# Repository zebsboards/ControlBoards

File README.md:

# ControlBoards
Control boards offered up over the years including 23port Lighting Boards, 24port High Power Boards and cabBlaster Boards

***Each Item is a separate Branch of the main hub***

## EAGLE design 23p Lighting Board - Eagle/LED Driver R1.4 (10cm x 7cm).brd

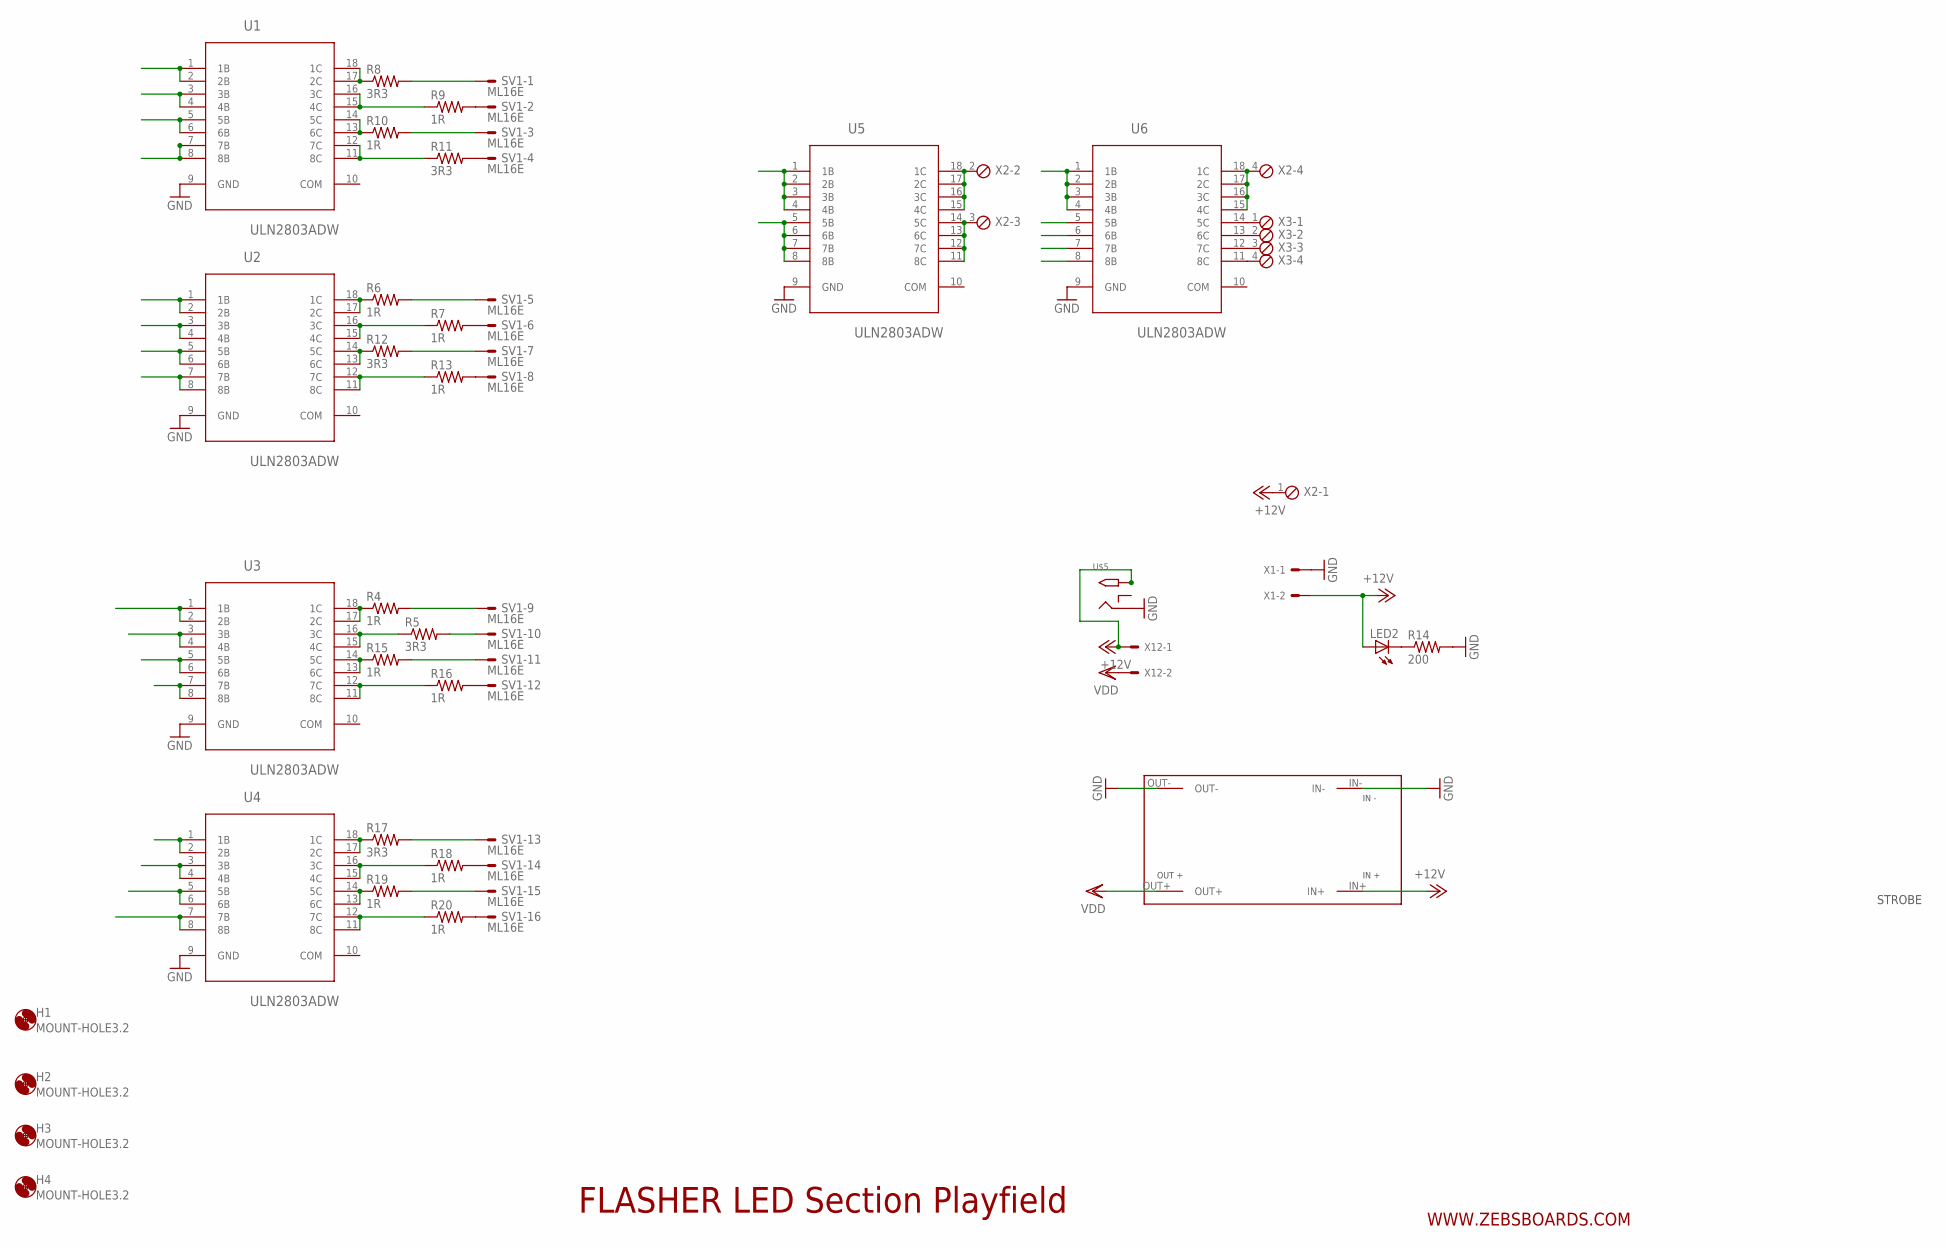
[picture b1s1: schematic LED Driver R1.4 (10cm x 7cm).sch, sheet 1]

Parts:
H1, H2, H3, H4: MOUNT-HOLE3.2; 3,2
LED2: LEDCHIP-LED0805; CHIP-LED0805
R4, R6, R7, R9, R10, R13, R15, R16, R18, R19, R20: 1R; R2010W
R5, R8, R11, R12, R17: 3R3; R2010W
R14: 200; M0805
SV1: ML16E; ML16
U1, U2, U3, U4, U5: ULN2803ADW; SOIC127P1030X265-18N
U6: ULN2803ADW; SOIC127P1030X265-18N; MPN ULN2803ADW
U$1: DC1ACONVERTER; DC1CONVERTER
U$5: 2.1MMJACKTHM; PJ-102A
X1, X12: KK-156-2
X2, X3: MPT4; 4POL254

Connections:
+12V: LED2.A, U$1.IN+, U$5.TIP, X1.2, X2.1, X12.1
D1: U1.1 (1B), U1.2 (2B); also elsewhere on the board
D2: U1.3 (3B), U1.4 (4B); also elsewhere on the board
D3: U1.5 (5B), U1.6 (6B); also elsewhere on the board
D4: U1.7 (7B), U1.8 (8B); also elsewhere on the board
D5: U2.1 (1B), U2.2 (2B); also elsewhere on the board
D6: U2.3 (3B), U2.4 (4B); also elsewhere on the board
D7: U2.5 (5B), U2.6 (6B); also elsewhere on the board
D8: U2.7 (7B), U2.8 (8B); also elsewhere on the board
D9: U3.1 (1B), U3.2 (2B); also elsewhere on the board
D10: U3.3 (3B), U3.4 (4B); also elsewhere on the board
D11: U3.5 (5B), U3.6 (6B); also elsewhere on the board
D12: U3.7 (7B), U3.8 (8B); also elsewhere on the board
D13: U4.1 (1B), U4.2 (2B); also elsewhere on the board
D14: U4.3 (3B), U4.4 (4B); also elsewhere on the board
D15: U4.5 (5B), U4.6 (6B); also elsewhere on the board
D16: U4.7 (7B), U4.8 (8B); also elsewhere on the board
D17: U5.1 (1B), U5.2 (2B), U5.3 (3B), U5.4 (4B); also elsewhere on the board
D18: U5.5 (5B), U5.6 (6B), U5.7 (7B), U5.8 (8B); also elsewhere on the board
D19: U6.1 (1B), U6.2 (2B), U6.3 (3B), U6.4 (4B); also elsewhere on the board
D20: U6.5 (5B); also elsewhere on the board
D21: U6.6 (6B); also elsewhere on the board
D22: U6.7 (7B); also elsewhere on the board
D23: U6.8 (8B); also elsewhere on the board
GND: R14.2, U1.9 (GND), U2.9 (GND), U3.9 (GND), U4.9 (GND), U5.9 (GND), U6.9 (GND), U$1.IN-, U$1.OUT-, U$5.RING, X1.1; also elsewhere on the board
unnamed: R9.1, U1.15 (4C), U1.16 (3C)
unnamed: R8.2, SV1.1
unnamed: R10.2, SV1.3
unnamed: R11.1, U1.11 (8C), U1.12 (7C)
unnamed: R4.1, U3.17 (2C), U3.18 (1C)
unnamed: R5.2, SV1.10
unnamed: R15.1, U3.13 (6C), U3.14 (5C)
unnamed: R8.1, U1.17 (2C), U1.18 (1C)
unnamed: R7.1, U2.15 (4C), U2.16 (3C)
unnamed: R6.2, SV1.5
unnamed: R12.2, SV1.7
unnamed: R13.1, U2.11 (8C), U2.12 (7C)
unnamed: R9.2, SV1.2
unnamed: R10.1, U1.13 (6C), U1.14 (5C)
unnamed: R11.2, SV1.4
unnamed: R6.1, U2.17 (2C), U2.18 (1C)
unnamed: R5.1, U3.15 (4C), U3.16 (3C)
unnamed: R4.2, SV1.9
unnamed: R15.2, SV1.11
unnamed: R16.1, U3.11 (8C), U3.12 (7C)
unnamed: R7.2, SV1.6
unnamed: R12.1, U2.13 (6C), U2.14 (5C)
unnamed: R13.2, SV1.8
unnamed: R16.2, SV1.12
unnamed: R18.1, U4.15 (4C), U4.16 (3C)
unnamed: LED2.C, R14.1
unnamed: R17.2, SV1.13
unnamed: R19.2, SV1.15
unnamed: R20.1, U4.11 (8C), U4.12 (7C)
unnamed: R17.1, U4.17 (2C), U4.18 (1C)
unnamed: R18.2, SV1.14
unnamed: R19.1, U4.13 (6C), U4.14 (5C)
unnamed: R20.2, SV1.16
unnamed: U5.15 (4C), U5.16 (3C), U5.17 (2C), U5.18 (1C), X2.2
unnamed: U5.11 (8C), U5.12 (7C), U5.13 (6C), U5.14 (5C), X2.3
unnamed: U6.15 (4C), U6.16 (3C), U6.17 (2C), U6.18 (1C), X2.4
unnamed: U6.14 (5C), X3.1
unnamed: U6.13 (6C), X3.2
unnamed: U6.12 (7C), X3.3
unnamed: U6.11 (8C), X3.4
VDD: U$1.OUT+, X12.2

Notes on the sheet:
FLASHER LED Section Playfield
WWW.ZEBSBOARDS.COM
STROBE

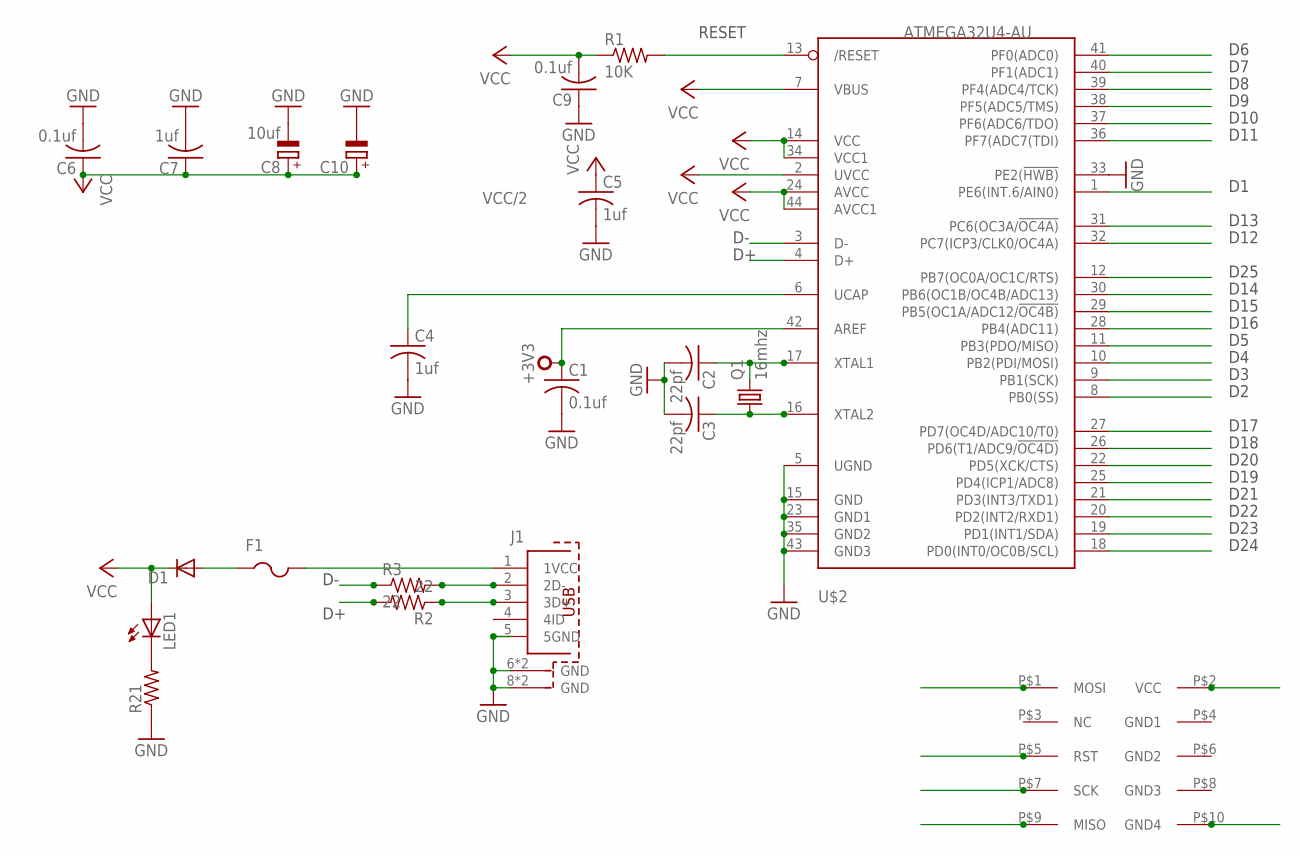
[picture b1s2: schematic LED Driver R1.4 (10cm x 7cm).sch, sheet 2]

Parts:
C1, C6, C9: 0.1uf; C0603
C2, C3: 22pf; C0603
C4, C5, C7: 1uf; C0603
C8: 10uf; A/3216-18W
C10: CPOL-EU153CLV-0605; 153CLV-0605
D1: DIODE-DO214AC; DO214AC
F1: PTCFUSE-1812; 1812
J1: 651005136521
LED1: LEDCHIPLED_0805; CHIPLED_0805
Q1: 16mhz; CTS406
R1: 10K; M0805
R2, R3: 22; M0805
R21: R-US_M0805; M0805
U$2: ATMEGA32U4-AU; TQFP44
U$4: 10PICSP

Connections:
+3V3: C1.1, U$2.42 (AREF)
D1: U$2.1 (PE6(INT.6/AIN0)); also elsewhere on the board
D2: U$2.8 (PB0(SS)); also elsewhere on the board
D3: U$2.9 (PB1(SCK)), U$4.P$7 (SCK); also elsewhere on the board
D4: U$2.10 (PB2(PDI/MOSI)), U$4.P$1 (MOSI); also elsewhere on the board
D5: U$2.11 (PB3(PDO/MISO)), U$4.P$9 (MISO); also elsewhere on the board
D6: U$2.41 (PF0(ADC0)); also elsewhere on the board
D7: U$2.40 (PF1(ADC1)); also elsewhere on the board
D8: U$2.39 (PF4(ADC4/TCK)); also elsewhere on the board
D9: U$2.38 (PF5(ADC5/TMS)); also elsewhere on the board
D10: U$2.37 (PF6(ADC6/TDO)); also elsewhere on the board
D11: U$2.36 (PF7(ADC7(TDI)); also elsewhere on the board
D12: U$2.32 (PC7(ICP3/CLK0/OC4A)); also elsewhere on the board
D13: U$2.31 (PC6(OC3A/!OC4A)); also elsewhere on the board
D14: U$2.30 (PB6(OC1B/OC4B/ADC13)); also elsewhere on the board
D15: U$2.29 (PB5(OC1A/ADC12/!OC4B)); also elsewhere on the board
D16: U$2.28 (PB4(ADC11)); also elsewhere on the board
D17: U$2.27 (PD7(OC4D/ADC10/T0)); also elsewhere on the board
D18: U$2.26 (PD6(T1/ADC9/!OC4D)); also elsewhere on the board
D19: U$2.25 (PD4(ICP1/ADC8)); also elsewhere on the board
D20: U$2.22 (PD5(XCK/CTS)); also elsewhere on the board
D21: U$2.21 (PD3(INT3/TXD1)); also elsewhere on the board
D22: U$2.20 (PD2(INT2/RXD1)); also elsewhere on the board
D23: U$2.19 (PD1(INT1/SDA)); also elsewhere on the board
D24: U$2.18 (PD0(INT0/OC0B/SCL))
D25: U$2.12 (PB7(OC0A/OC1C/RTS))
D+: R2.2, U$2.4 (D+)
D-: R3.1, U$2.3 (D-)
GND: C1.2, C2.2, C3.2, C4.2, C5.2, C6.2, C7.2, C8.-, C9.1, C10.-, J1.5 (5GND), J1.6 (GND), J1.7 (GND), J1.8 (GND), J1.9 (GND), R21.1, U$2.5 (UGND), U$2.15 (GND), U$2.23 (GND1), U$2.33 (PE2(!HWB)), U$2.35 (GND2), U$2.43 (GND3), U$4.P$10 (GND4); also elsewhere on the board
unnamed: C2.1, Q1.3 (2), U$2.17 (XTAL1)
unnamed: C3.1, Q1.1, U$2.16 (XTAL2)
unnamed: C4.1, U$2.6 (UCAP)
unnamed: J1.2 (2D-), R3.2
unnamed: J1.3 (3D+), R2.1
unnamed: F1.2, J1.1 (1VCC)
unnamed: D1.A, F1.1
unnamed: LED1.C, R21.2
RST: R1.2, U$2.13 (/RESET), U$4.P$5 (RST)
VCC: C5.1, C6.1, C7.1, C8.+, C9.2, C10.+, D1.C, LED1.A, R1.1, U$2.2 (UVCC), U$2.7 (VBUS), U$2.14 (VCC), U$2.24 (AVCC), U$2.34 (VCC1), U$2.44 (AVCC1), U$4.P$2 (VCC)

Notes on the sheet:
VCC/2
RESET
D11
D16
D15
D14
D12
D10
D13
D25
D17
D18
D20
D21
D22
D23
D24
D19

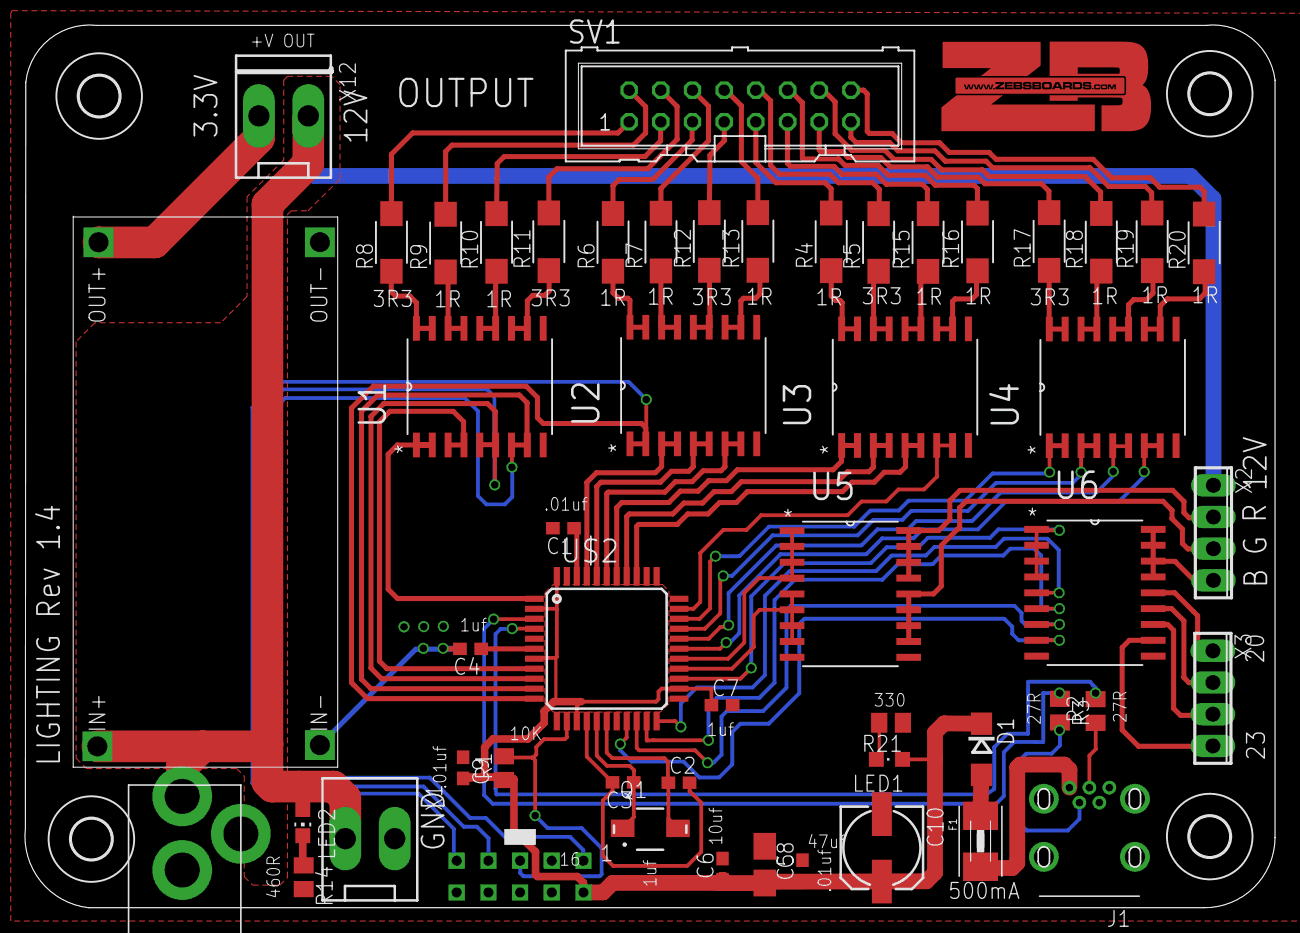
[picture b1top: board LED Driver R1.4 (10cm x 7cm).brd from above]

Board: 2 copper layers, 100.2 x 70.8 mm, 57 parts (0 on the bottom side), 79 nets.

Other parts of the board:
U$3: ZB_LOGO_SMALL_COPPER

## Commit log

2025-07-10 Direct Output cabBlaster Driver files
2025-07-10 cbBlaster Arduino Source files
2025-07-10 VS 2019 Configuration Utility Source code

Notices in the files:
parts and their libraries:
Wurth_Elektronik_Electromechanic_Input-O: Copyright: Würth Elektronik
